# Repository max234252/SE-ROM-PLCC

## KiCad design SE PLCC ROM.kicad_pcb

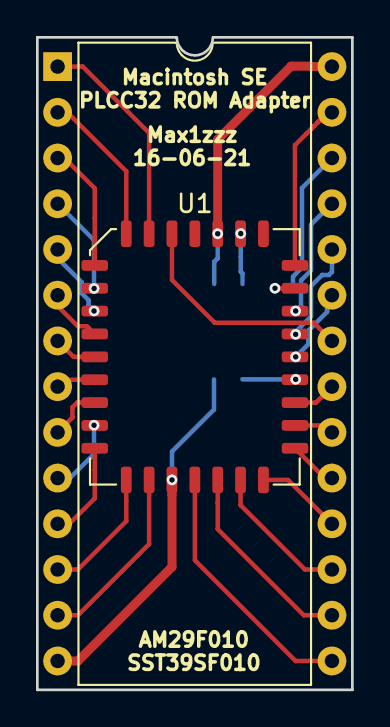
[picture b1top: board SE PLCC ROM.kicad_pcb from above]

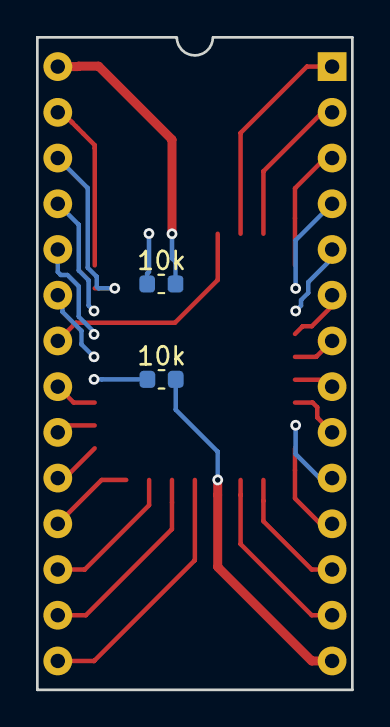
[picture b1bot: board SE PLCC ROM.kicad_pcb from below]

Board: 2 copper layers, 17.5 x 36.2 mm, 4 parts (2 on the bottom side), 30 nets.

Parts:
J1: Conn_02x14_Counter_Clockwise; DIP-28_W15.24mm
R1, R2: 10k; R_0603_1608Metric
U1: SST39SF010; PLCC-32_11.4x14.0mm_P1.27mm

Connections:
+5V: J1.28, R1.1, U1.32
/A0: J1.10, U1.12
/A1: J1.9, U1.11
/A2: J1.8, U1.10
/A3: J1.7, U1.9
/A4: J1.6, U1.8
/A5: J1.5, U1.7
/A6: J1.4, U1.6
/A7: J1.3, U1.5
/A8: J1.25, U1.27
/A9: J1.24, U1.26
/A10: J1.21, U1.23
/A11: J1.23, U1.25
/A12: J1.2, U1.4
/A13: J1.26, U1.28
/A14: J1.27, U1.29
/A15: J1.1, U1.3
/A16: J1.22, U1.2
/D0: J1.11, U1.13
/D1: J1.12, U1.14
/D2: J1.13, U1.15
/D3: J1.15, U1.17
/D4: J1.16, U1.18
/D5: J1.17, U1.19
/D6: J1.18, U1.20
/D7: J1.19, U1.21
GND: J1.14, R2.2, U1.16
unnamed: J1.20, U1.22
unnamed: R1.2, U1.31
unnamed: R2.1, U1.24
